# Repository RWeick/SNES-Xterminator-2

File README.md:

# SNES-Xterminator-2
The Kicad files, rom dump, GAL JEDEC, and recovered AMI 18CV8PC logic for the SNES Xterminator 2 cheat device. I have redone the trace layout and added additional pads for SMD components.  
Standard jumper configuration: Pads 2, 4, 6, 8, 10, and 12 are shorted. The original firmware is available here as well as a modified one which translates it into English and is otherwise the same as the original.

Main Board PCB Thickness: 1.2 mm  
Cartridge Connector Board PCB Thickness: 1.6 mm

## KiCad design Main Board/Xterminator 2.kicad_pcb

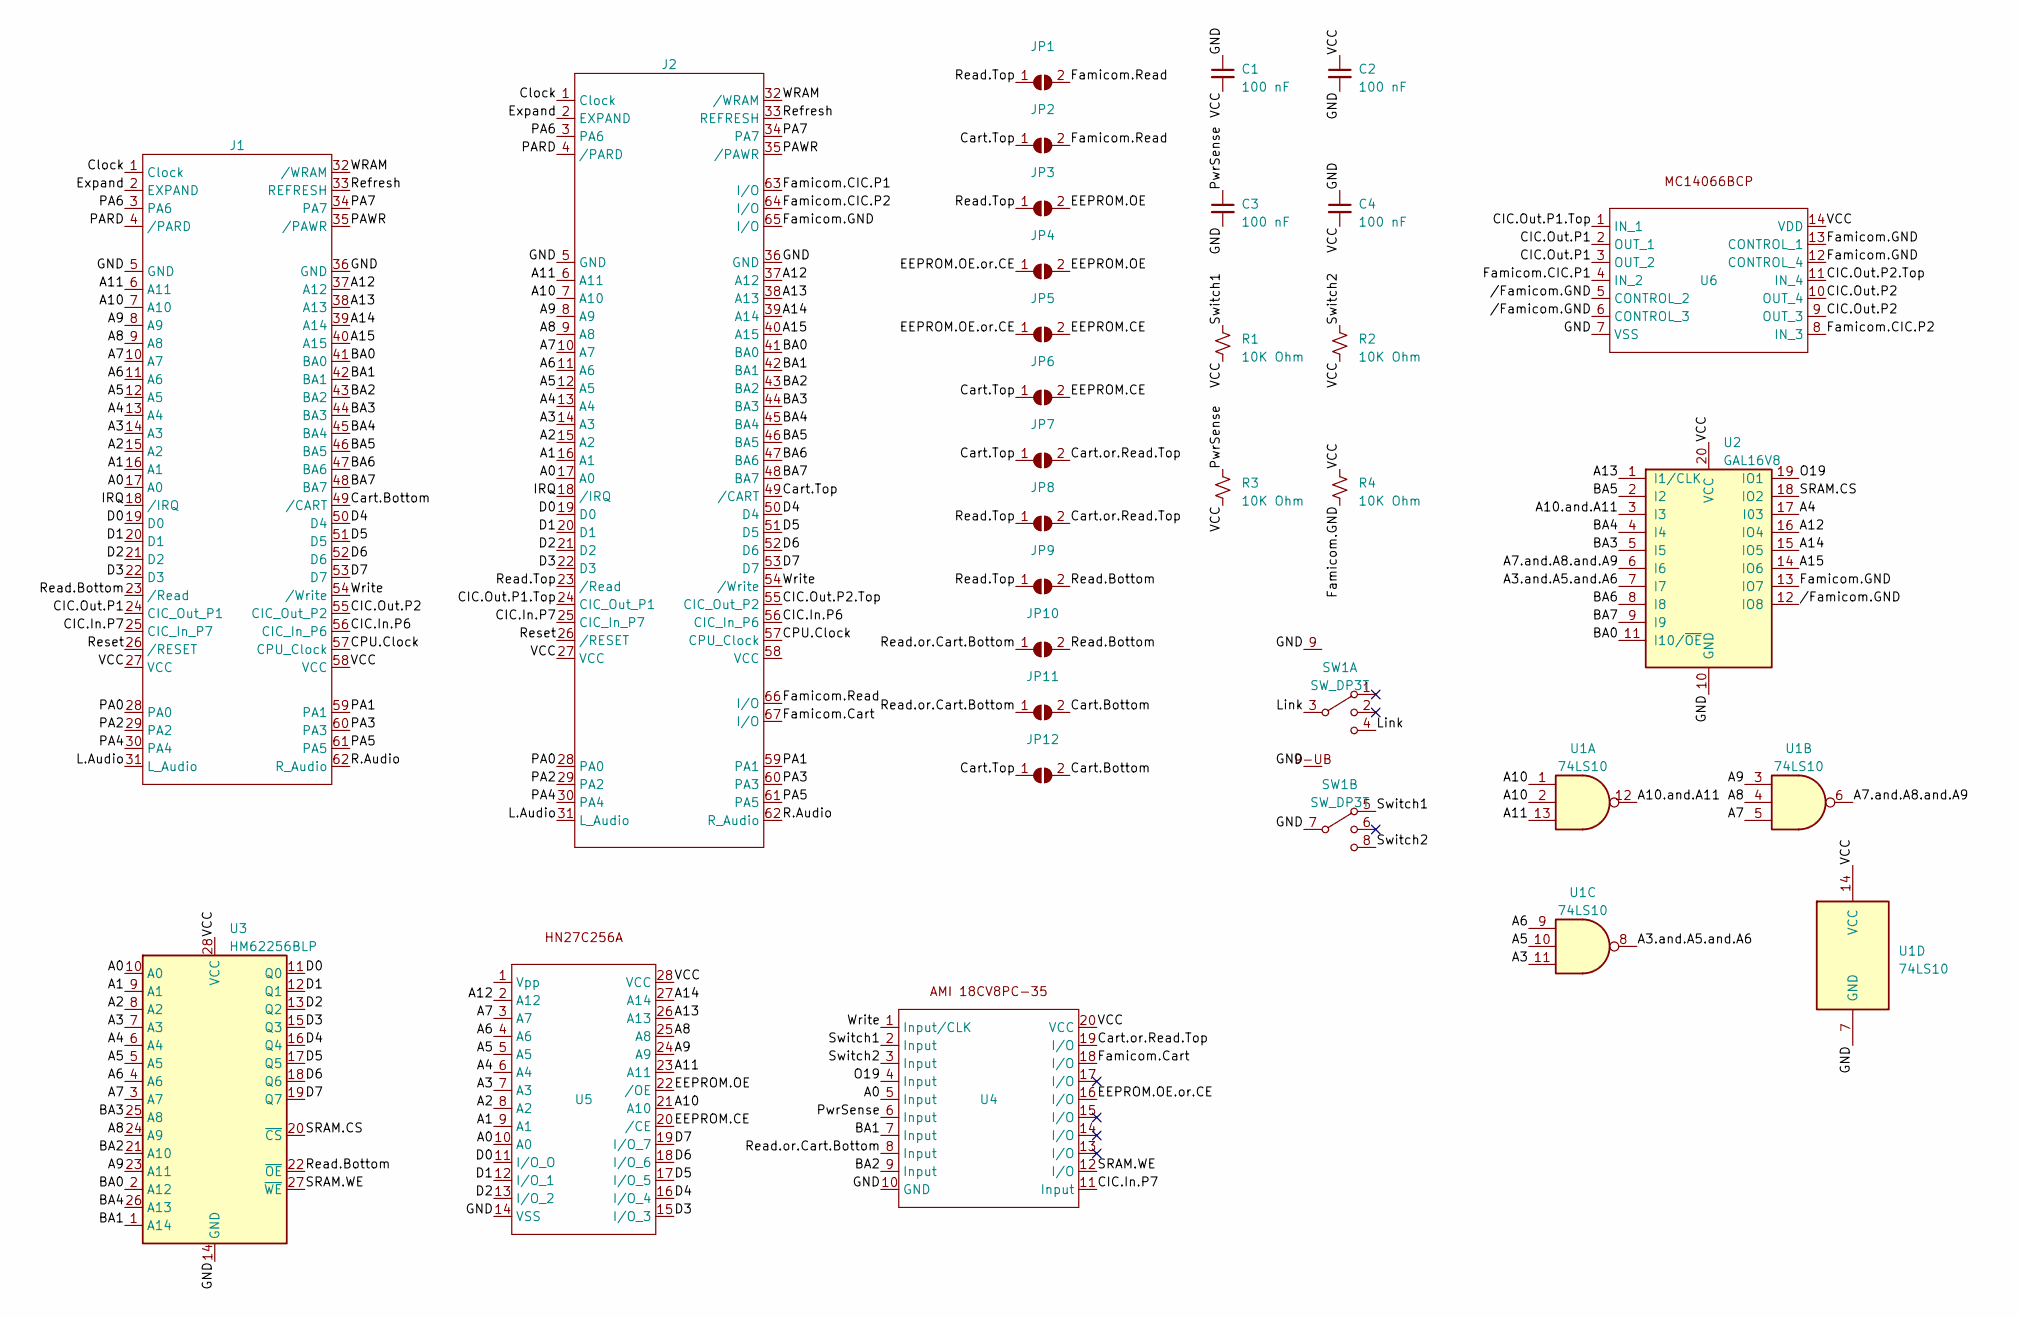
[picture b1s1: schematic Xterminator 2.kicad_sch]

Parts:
C1, C2, C3, C4: 100 nF; SMD Cap-Res
J1: SNES Edge Connector
J2: Upper Edge Connector
JP1, JP2, JP3, JP4, JP5, JP6, JP7, JP8, JP9, JP10, JP11, JP12: SolderJumper_2_Open; Jumper Pads
R1, R2, R3, R4: 10K Ohm; SMD Cap-Res
SW1: SW_DP3T; Switch
U1: 74LS10
U2: GAL16V8
U3: HM62256BLP; HM62256
U4: 18CVP8C
U5: HN27C256
U6: MC14066BCP

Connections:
/A0: J1.17 (A0), J2.17 (A0), U3.10 (A0), U4.5 (Input), U5.10 (A0)
/A1: J1.16 (A1), J2.16 (A1), U3.9 (A1), U5.9 (A1)
/A2: J1.15 (A2), J2.15 (A2), U3.8 (A2), U5.8 (A2)
/A3: J1.14 (A3), J2.14 (A3), U1.11, U3.7 (A3), U5.7 (A3)
/A3.and.A5.and.A6: U1.8, U2.7 (I7)
/A4: J1.13 (A4), J2.13 (A4), U2.17 (I03), U3.6 (A4), U5.6 (A4)
/A5: J1.12 (A5), J2.12 (A5), U1.10, U3.5 (A5), U5.5 (A5)
/A6: J1.11 (A6), J2.11 (A6), U1.9, U3.4 (A6), U5.4 (A6)
/A7: J1.10 (A7), J2.10 (A7), U1.5, U3.3 (A7), U5.3 (A7)
/A7.and.A8.and.A9: U1.6, U2.6 (I6)
/A8: J1.9 (A8), J2.9 (A8), U1.4, U3.24 (A9), U5.25 (A8)
/A9: J1.8 (A9), J2.8 (A9), U1.3, U3.23 (A11), U5.24 (A9)
/A10: J1.7 (A10), J2.7 (A10), U1.1, U1.2, U5.21 (A10)
/A10.and.A11: U1.12, U2.3 (I3)
/A11: J1.6 (A11), J2.6 (A11), U1.13, U5.23 (A11)
/A12: J1.37 (A12), J2.37 (A12), U2.16 (IO4), U5.2 (A12)
/A13: J1.38 (A13), J2.38 (A13), U2.1 (I1/CLK), U5.26 (A13)
/A14: J1.39 (A14), J2.39 (A14), U2.15 (IO5), U5.27 (A14)
/A15: J1.40 (A15), J2.40 (A15), U2.14 (IO6)
/BA0: J1.41 (BA0), J2.41 (BA0), U2.11 (I10/~OE), U3.2 (A12)
/BA1: J1.42 (BA1), J2.42 (BA1), U3.1 (A14), U4.7 (Input)
/BA2: J1.43 (BA2), J2.43 (BA2), U3.21 (A10), U4.9 (Input)
/BA3: J1.44 (BA3), J2.44 (BA3), U2.5 (I5), U3.25 (A8)
/BA4: J1.45 (BA4), J2.45 (BA4), U2.4 (I4), U3.26 (A13)
/BA5: J1.46 (BA5), J2.46 (BA5), U2.2 (I2)
/BA6: J1.47 (BA6), J2.47 (BA6), U2.8 (I8)
/BA7: J1.48 (BA7), J2.48 (BA7), U2.9 (I9)
/CIC.In.P6: J1.56 (CIC_In_P6), J2.56 (CIC_In_P6)
/CIC.In.P7: J1.25 (CIC_In_P7), J2.25 (CIC_In_P7), U4.11 (Input)
/CIC.Out.P1: J1.24 (CIC_Out_P1), U6.2 (OUT_1), U6.3 (OUT_2)
/CIC.Out.P1.Top: J2.24 (CIC_Out_P1), U6.1 (IN_1)
/CIC.Out.P2: J1.55 (CIC_Out_P2), U6.9 (OUT_3), U6.10 (OUT_4)
/CIC.Out.P2.Top: J2.55 (CIC_Out_P2), U6.11 (IN_4)
/CPU.Clock: J1.57 (CPU_Clock), J2.57 (CPU_Clock)
/Cart.Bottom: J1.49 (/CART), JP11.2 (B), JP12.2 (B)
/Cart.Top: J2.49 (/CART), JP2.1 (A), JP6.1 (A), JP7.1 (A), JP12.1 (A)
/Cart.or.Read.Top: JP7.2 (B), JP8.2 (B), U4.19 (I/O)
/Clock: J1.1 (Clock), J2.1 (Clock)
/D0: J1.19 (D0), J2.19 (D0), U3.11 (Q0), U5.11 (I/O_O)
/D1: J1.20 (D1), J2.20 (D1), U3.12 (Q1), U5.12 (I/O_1)
/D2: J1.21 (D2), J2.21 (D2), U3.13 (Q2), U5.13 (I/O_2)
/D3: J1.22 (D3), J2.22 (D3), U3.15 (Q3), U5.15 (I/O_3)
/D4: J1.50 (D4), J2.50 (D4), U3.16 (Q4), U5.16 (I/O_4)
/D5: J1.51 (D5), J2.51 (D5), U3.17 (Q5), U5.17 (I/O_5)
/D6: J1.52 (D6), J2.52 (D6), U3.18 (Q6), U5.18 (I/O_6)
/D7: J1.53 (D7), J2.53 (D7), U3.19 (Q7), U5.19 (I/O_7)
/EEPROM.CE: JP5.2 (B), JP6.2 (B), U5.20 (/CE)
/EEPROM.OE: JP3.2 (B), JP4.2 (B), U5.22 (/OE)
/EEPROM.OE.or.CE: JP4.1 (A), JP5.1 (A), U4.16 (I/O)
/Expand: J1.2 (EXPAND), J2.2 (EXPAND)
/Famicom.CIC.P1: J2.63 (I/O), U6.4 (IN_2)
/Famicom.CIC.P2: J2.64 (I/O), U6.8 (IN_3)
/Famicom.Cart: J2.67 (I/O), U4.18 (I/O)
/Famicom.GND: J2.65 (I/O), R4.2, U2.13 (IO7), U6.12 (CONTROL_4), U6.13 (CONTROL_1)
/Famicom.Read: J2.66 (I/O), JP1.2 (B), JP2.2 (B)
/GND: C1.1, C2.2, C3.2, C4.1, J1.5 (GND), J1.36 (GND), J2.5 (GND), J2.36 (GND), SW1.7, SW1.9 (Shield), SW1.9-UB (Shield), U1.7 (GND), U2.10 (GND), U3.14 (GND), U4.10 (GND), U5.14 (VSS), U6.7 (VSS)
/IRQ: J1.18 (/IRQ), J2.18 (/IRQ)
/L.Audio: J1.31 (L_Audio), J2.31 (L_Audio)
/Link: SW1.3, SW1.4
/O19: U2.19 (IO1), U4.4 (Input)
/PA0: J1.28 (PA0), J2.28 (PA0)
/PA1: J1.59 (PA1), J2.59 (PA1)
/PA2: J1.29 (PA2), J2.29 (PA2)
/PA3: J1.60 (PA3), J2.60 (PA3)
/PA4: J1.30 (PA4), J2.30 (PA4)
/PA5: J1.61 (PA5), J2.61 (PA5)
/PA6: J1.3 (PA6), J2.3 (PA6)
/PA7: J1.34 (PA7), J2.34 (PA7)
/PARD: J1.4 (/PARD), J2.4 (/PARD)
/PAWR: J1.35 (/PAWR), J2.35 (/PAWR)
/PwrSense: C3.1, R3.1, U4.6 (Input)
/R.Audio: J1.62 (R_Audio), J2.62 (R_Audio)
/Read.Bottom: J1.23 (/Read), JP9.2 (B), JP10.2 (B), U3.22 (~OE)
/Read.Top: J2.23 (/Read), JP1.1 (A), JP3.1 (A), JP8.1 (A), JP9.1 (A)
/Read.or.Cart.Bottom: JP10.1 (A), JP11.1 (A), U4.8 (Input)
/Refresh: J1.33 (REFRESH), J2.33 (REFRESH)
/Reset: J1.26 (/RESET), J2.26 (/RESET)
/SRAM.CS: U2.18 (IO2), U3.20 (~CS)
/SRAM.WE: U3.27 (~WE), U4.12 (I/O)
/Switch1: R1.1, SW1.5, U4.2 (Input)
/Switch2: R2.1, SW1.8, U4.3 (Input)
/VCC: C1.2, C2.1, C4.2, J1.27 (VCC), J1.58 (VCC), J2.27 (VCC), R1.2, R2.2, R3.2, R4.1, U1.14 (VCC), U2.20 (VCC), U3.28 (VCC), U4.20 (VCC), U5.28 (VCC), U6.14 (VDD)
/WRAM: J1.32 (/WRAM), J2.32 (/WRAM)
/Write: J1.54 (/Write), J2.54 (/Write), U4.1 (Input/CLK)
//Famicom.GND: U2.12 (IO8), U6.5 (CONTROL_2), U6.6 (CONTROL_3)

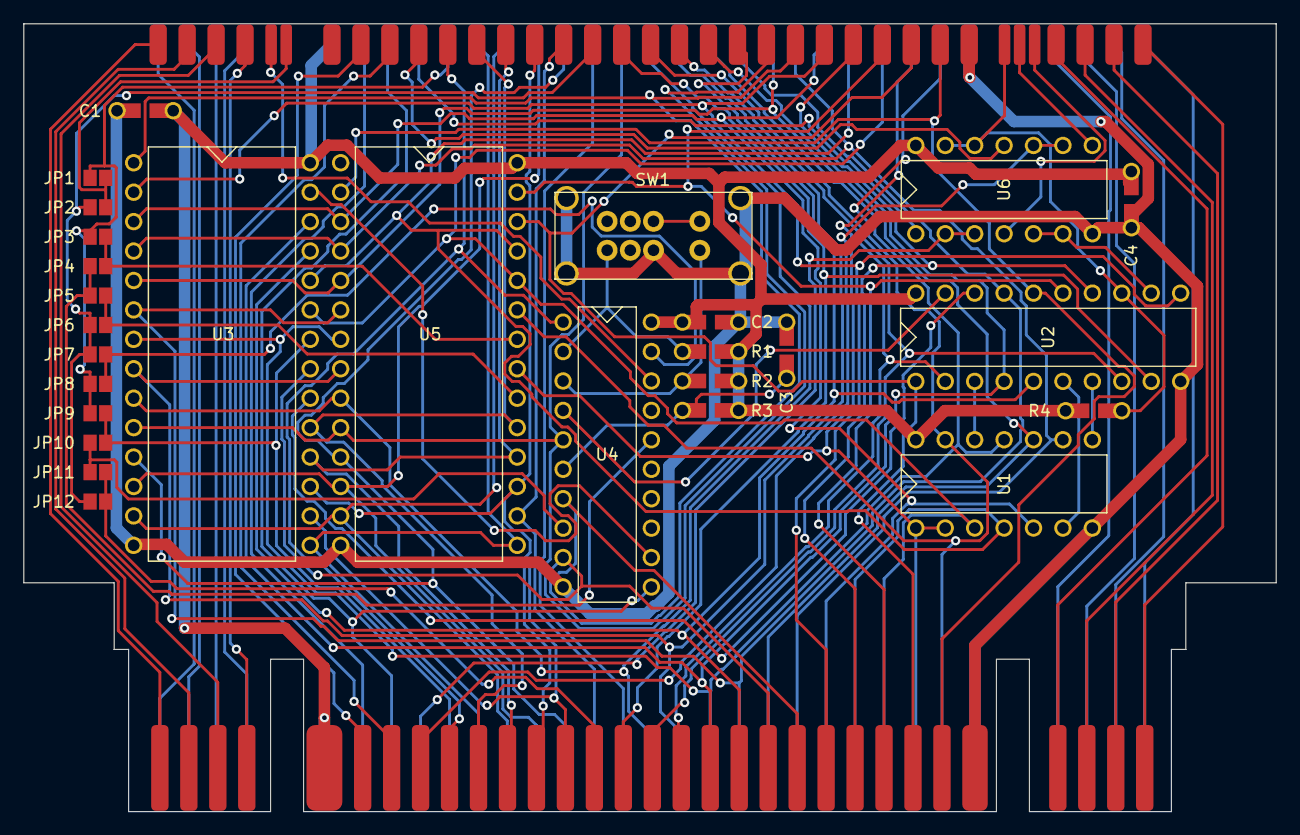
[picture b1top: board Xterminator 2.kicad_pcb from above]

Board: 2 copper layers, 108.1 x 68.0 mm, 29 parts (0 on the bottom side), 85 nets.

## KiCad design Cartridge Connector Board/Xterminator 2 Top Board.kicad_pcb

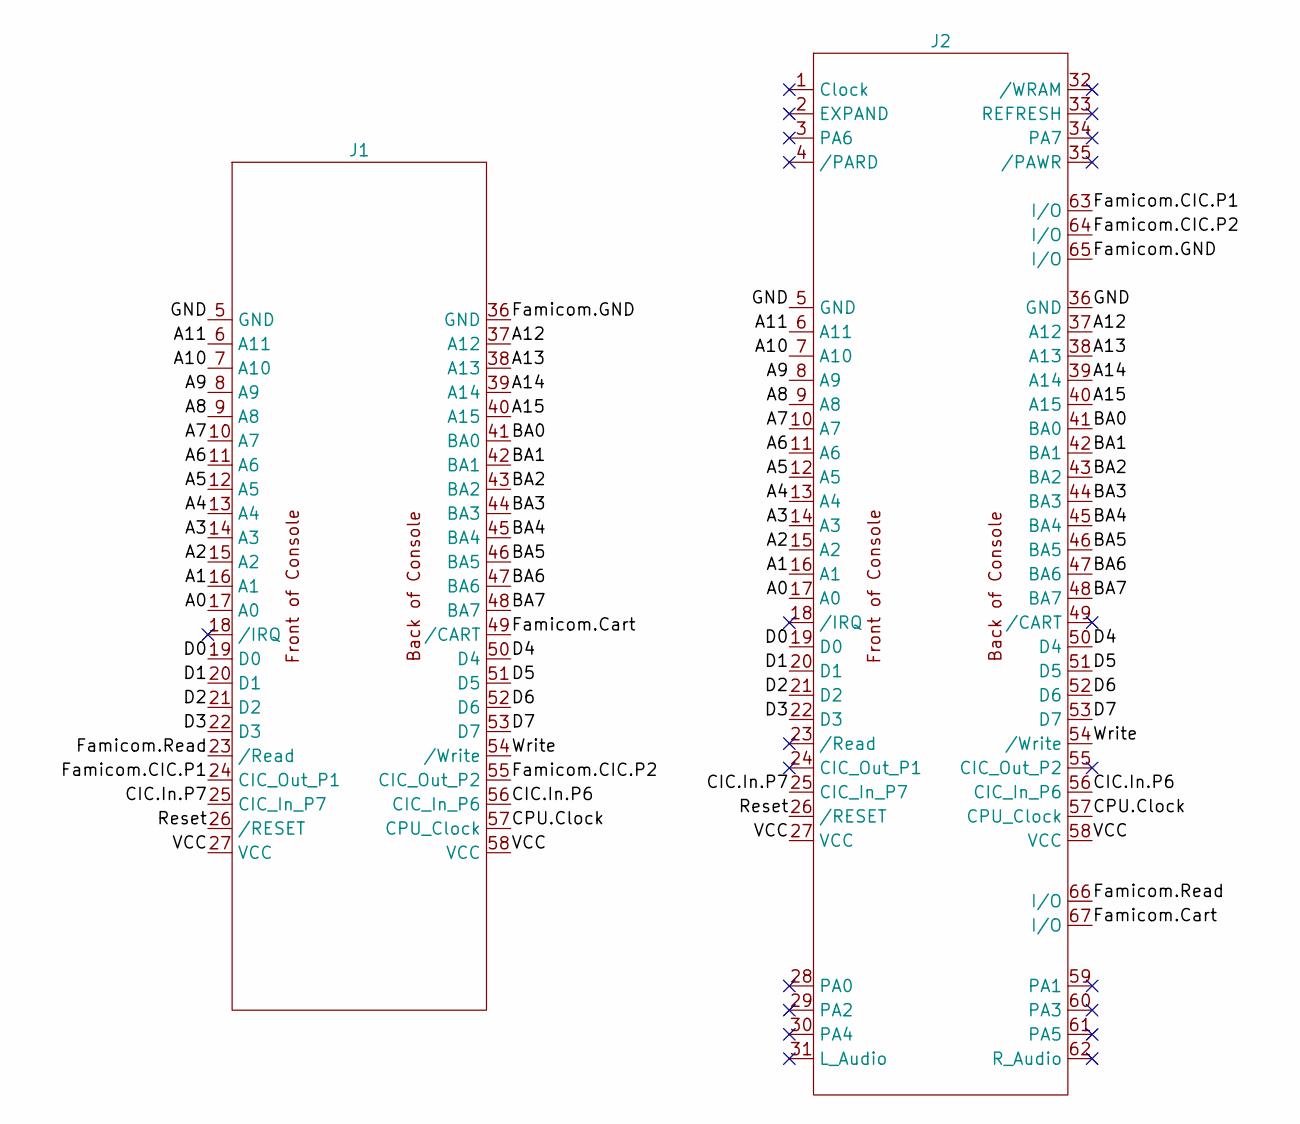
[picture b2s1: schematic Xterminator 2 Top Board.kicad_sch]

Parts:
J1: Super Famicom Cartridge Slot
J2: SNES Cartridge Slot

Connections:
/A0: J1.17 (A0), J2.17 (A0)
/A1: J1.16 (A1), J2.16 (A1)
/A2: J1.15 (A2), J2.15 (A2)
/A3: J1.14 (A3), J2.14 (A3)
/A4: J1.13 (A4), J2.13 (A4)
/A5: J1.12 (A5), J2.12 (A5)
/A6: J1.11 (A6), J2.11 (A6)
/A7: J1.10 (A7), J2.10 (A7)
/A8: J1.9 (A8), J2.9 (A8)
/A9: J1.8 (A9), J2.8 (A9)
/A10: J1.7 (A10), J2.7 (A10)
/A11: J1.6 (A11), J2.6 (A11)
/A12: J1.37 (A12), J2.37 (A12)
/A13: J1.38 (A13), J2.38 (A13)
/A14: J1.39 (A14), J2.39 (A14)
/A15: J1.40 (A15), J2.40 (A15)
/BA0: J1.41 (BA0), J2.41 (BA0)
/BA1: J1.42 (BA1), J2.42 (BA1)
/BA2: J1.43 (BA2), J2.43 (BA2)
/BA3: J1.44 (BA3), J2.44 (BA3)
/BA4: J1.45 (BA4), J2.45 (BA4)
/BA5: J1.46 (BA5), J2.46 (BA5)
/BA6: J1.47 (BA6), J2.47 (BA6)
/BA7: J1.48 (BA7), J2.48 (BA7)
/CIC.In.P6: J1.56 (CIC_In_P6), J2.56 (CIC_In_P6)
/CIC.In.P7: J1.25 (CIC_In_P7), J2.25 (CIC_In_P7)
/CPU.Clock: J1.57 (CPU_Clock), J2.57 (CPU_Clock)
/D0: J1.19 (D0), J2.19 (D0)
/D1: J1.20 (D1), J2.20 (D1)
/D2: J1.21 (D2), J2.21 (D2)
/D3: J1.22 (D3), J2.22 (D3)
/D4: J1.50 (D4), J2.50 (D4)
/D5: J1.51 (D5), J2.51 (D5)
/D6: J1.52 (D6), J2.52 (D6)
/D7: J1.53 (D7), J2.53 (D7)
/Famicom.CIC.P1: J1.24 (CIC_Out_P1), J2.63 (I/O)
/Famicom.CIC.P2: J1.55 (CIC_Out_P2), J2.64 (I/O)
/Famicom.Cart: J1.49 (/CART), J2.67 (I/O)
/Famicom.GND: J1.36 (GND), J2.65 (I/O)
/Famicom.Read: J1.23 (/Read), J2.66 (I/O)
/GND: J1.5 (GND), J2.5 (GND), J2.36 (GND)
/Reset: J1.26 (/RESET), J2.26 (/RESET)
/VCC: J1.27 (VCC), J1.58 (VCC), J2.27 (VCC), J2.58 (VCC)
/Write: J1.54 (/Write), J2.54 (/Write)

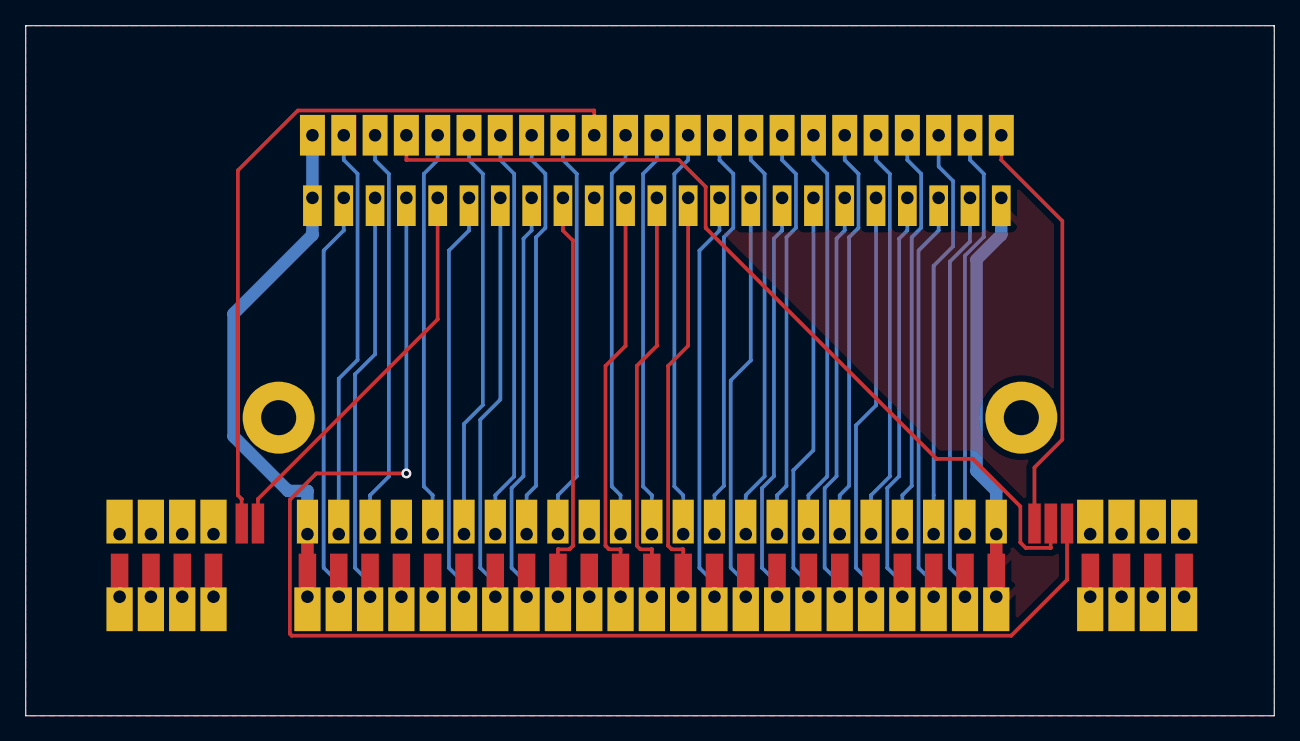
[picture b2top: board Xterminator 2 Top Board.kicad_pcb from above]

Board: 2 copper layers, 99.7 x 55.1 mm, 4 parts (0 on the bottom side), 44 nets.

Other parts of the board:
Hole1, Hole2: Screw Hole
